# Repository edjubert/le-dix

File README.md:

# Le Dix
A 10 keys keyboard layout

## Keyboard
I'm currently daily using this layout on the [ZSA Moonlander](https://www.zsa.io/moonlander/). This allow me to experiment a lot all possibilities.
I'm working on a physical keyboard, but it's still a work in progress.
[Here is the Github link of the project](https://github.com/edjubert/le-dix_keyboard). It might not be accessible yet.

## Conception
The main idea is to create a 10 keys keyboard usable for a day to day usage.
I transposed the Colemak philosophy to a 10 keys keyboard but without steno typing.
I found stenography extremely convenient for fast typing.
But when it comes to casual computer usage (ctrl+c, ctrl+v, change workspace, navigate a web browser, coding, etc) you can feel it was not made for that.

In a journey to "always fewer keys", I started with a 70 keys, to a Corne (42 keys), to a Corne mini (36 keys), to a Ferris Sweep (34 keys).
Even if the Ferris Sweep was super comfy, I wondered "Is there a usable, fewer keys keyboard out there?"

So I tried ARTSEY, an 8 keys, one handed keyboard.
It is a great project but, to me, it can put too much stress on one hand.
I tried to double the ARTSEY so I can have a full keyboard under each hand, so I can alternate typing on each letter.
But I found it really demanding to map two keyboard in my head and to create muscle memory to alternate strokes.

I tried ASETNIOP, a 10 keys, steno oriented keyboard.
The fact that each chord is using both hands create a limitation for a normal, non-steno usage.

As a Colemak user for 7 years, I remembered that this layout optimized the usage of the home row, alternation of hands and allow rolling most common combination ("en", "ion", ...)
With that in mind, I transposed the home row to an 8 keys one, ordered letters by usage and repected side position on the Colemak layout (letters under the left hand on the Colemak layout will stay under the left hand on the Croissants layout)
It is important that each letter stay a chord made by one hand (in opposition to ASETNIOP philosophy to use both hands). It will maximize the alternation of hands and optimize speed.

Once letters positionned, I created a list of chords ordered by accessibility and difficulty.
Every chord is mirrored on each hand, to facilitate the learning of chords.
The idea is to attribute the most accessible chords to the most used letters.

The result is a layout that I use full time right now, at a speed of 50 WPM after two weeks (I was at 65 WPM on Colemak so I'm not a super fast typer).
The layout is so comfy that I also stop using the mouse to use the one on the board and I do all navigation, media, shortcuts, mouse, etc with it.

## Moonlander
I'm currently using this layout on the ZSA Moonlander.
You can test it by flashing these links: 
- [Colemak](https://configure.zsa.io/moonlander/layouts/JzzyW/latest/0)
- [QWERTY](https://configure.zsa.io/moonlander/layouts/jvDM7/latest/0)

### Layers

[See here for a dark theme version](./dark.md)

#### Main
##### Colemak

##### QWERTY

#### Numeric

#### F keys

#### Symbols

#### Navigation

#### Mouse

#### Wheel

#### Media

## Full diagram

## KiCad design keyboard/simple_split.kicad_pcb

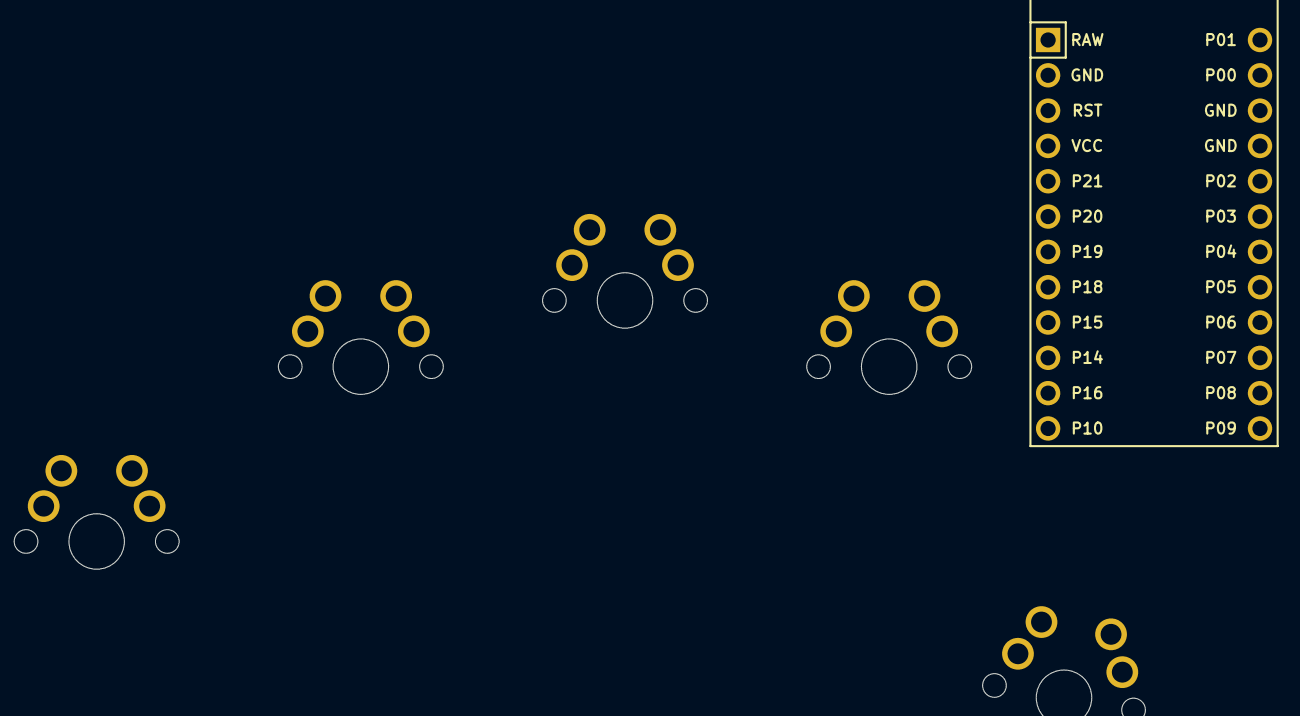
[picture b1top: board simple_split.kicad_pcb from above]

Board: 2 copper layers, 6 parts (0 on the bottom side), 6 nets, no tracks yet.

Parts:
MCU1: ProMicro
S1, S2, S3, S4, S5: MX

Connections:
GND: MCU1.2, MCU1.15, MCU1.16, S1.1, S2.1, S3.1, S4.1, S5.1
matrix_index_bottom: MCU1.19, S4.2
matrix_middle_bottom: MCU1.18, S3.2
matrix_pinky_bottom: MCU1.13, S1.2
matrix_ring_bottom: MCU1.17, S2.2
thumb_tucky: MCU1.21, S5.2

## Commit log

2024-02-07 first push
2024-02-07 Added Oryx Moonlander link
2024-02-09 Added diagrams and oryx screenshots
2024-02-09 Fixed num layer combos diagram
2024-02-09 Fix num layer combo diagram
2024-02-14 Added QWERTY Oryx link
2024-02-27 Updated QWERTY and Colemak diagrams
2024-02-27 updated diagrams
    - numeric (light, dark)
    - f keys (light, dark)
    - symbols (light, dark)
2024-02-28 deleted keyboard folder
2024-02-28 added light theme diagrams on README.md
